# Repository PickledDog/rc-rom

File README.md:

# rc-rom
 ROM card for RC2014

(version 1.0 shown, current version 1.1 has a second LED for paging status)

## Overview
This RC2014-compatible board provides ROM from an EPROM or EEPROM, with 8k/16k/32k granularity. The ROM can be paged out and replaced by RAM, when combined with a compatible RAM card. A user-controllable LED is also provided.

## ROM
This board provides ROM to a RC2014 system. It does not provide RAM, but can interact with a compatible RAM card. The [official RC2014 64K RAM](https://rc2014.co.uk/modules/64k-ram/) card is supported, as is the [PD101 board](https://github.com/PickledDog/rc-z80ram), which it was designed in tandem with.

## Paging
Paging (the ability to replace the ROM with RAM) is implemented using the *PAGE* signal in the RC2014 Enhanced Bus. This is the only Enhanced Bus signal required - if you're using a Standard Bus backplane (or don't intend to install a two-row header), a wire can be used to link the page signals between this board and the RAM (the pin in question is #4 of the 10 Enhanced pins).

If the *PAGE* signal cannot be connected, any RAM in the system will need to be configured to not appear in the lower memory addresses used by the ROM - consult the documentation of the RAM board. PD101 *cannot* selectively disable memory like this, and requires the PAGE signal in order to work with this board. Alternatively, [PD106](https://github.com/PickledDog/rc-ramrom) can be built instead of this board, since it has RAM built-in and doesn't require the Enhanced bus.

## Software compatibility
The board presents two I/O devices to the system - the LED at base port 0x08, and the ROM paging at 0x38. The LED appears at the same address as the LED of the [SC114 Motherboard](https://smallcomputercentral.wordpress.com/sc114-documentation/), and the ROM control address is common to most Z80 retrocomputers (the official RC2014 RAM/ROM cards included). As such, this board is compatible with most SC114 software, as well as Grant Searle's CP/M loader. LED is active low (lights by default) - writing a **1** to 0x08 turns it off. Writing a **1** to 0x38 disables the ROM.

## Chip support
The board supports 27C64, 27C128, 27C256, and 27C512 EPROMs, as well as 28C64 and 28C256 EEPROMs. Other chips with similar pinouts will *probably* work, but are untested. 150ns parts (like most 28C256s) are running at the edge of their specification in a standard 7.3Mhz system, and may require lowering the CPU clock. The [27C256](https://www.mouser.com/ProductDetail/AT27C256R-70PU/), [27C512](https://www.mouser.com/ProductDetail/AT27C512R-70PU/), and [28C256](https://www.mouser.com/ProductDetail/AT28C256-15PU/) can be purchased new.

## Firmware
Most (if not all) [RC2014 ROM images](https://github.com/RC2014Z80/RC2014/tree/master/ROMs) can be used unmodified (selecting the right images for your serial board, of course). Stephen C Cousins' excellent [Small Computer Monitor](https://smallcomputercentral.wordpress.com/small-computer-monitor/) can be used as well - all of the R* configurations are supported. You will need an EPROM programmer (for example, a [TL866](https://www.ebay.com/sch/i.html?_nkw=tl866ii+plus)) to load the ROM images onto a chip.

## Jumper settings
Refer to the front of the board for detailed jumper setting instructions.

## Part selection
Bill Of Materials and part references are below. In order to make the 50-pin RC2014 Enhanced bus connector, you'll need to take a 2x40-pin right-angle header and pull out most of the pins from the top row (needle-nose pliers work well). I recommend using gold-plated header for this - I use these ones from [Pololu](https://www.pololu.com/product/2668) or [Sparkfun](https://www.sparkfun.com/products/12792). The jumper headers can be snapped from regular (or double-row) breakaway header, for which eBay is substantially cheaper; the Mouser listings are provided for convenience.

The specified parts are just the ones I used, and can be substituted as needed - Mouser links provided for convenience and reference. A ZIF socket can be used for the EPROM - these are best [sourced from eBay](https://www.ebay.com/sch/i.html?_nkw=28+pin+zif+socket).

| Reference | Value | Qty | Mouser link |
| --------- | ----- | --- | ----------- |
| C1-C4 | 100nF ceramic | 4 | [KEMET C315C104M5U5TA](https://www.mouser.com/ProductDetail/C315C104M5U5TA7303) |
| D1 | 3mm yellow LED | 1 | [Lite-On LTL-4251N](https://www.mouser.com/ProductDetail/LTL-4251N) |
| D2 | 3mm green LED | 1 | [Lite-On LTL-4231N](https://www.mouser.com/ProductDetail/LTL-4231N) |
| J1/2 | 2x40 right-angle header | 1 | [3M 2380-5121TG](https://www.mouser.com/ProductDetail/2380-5121TG) |
| JP1/2 | 2x3 header | 1 | [Amphenol 10129381-906002BLF](https://www.mouser.com/ProductDetail/10129381-906002BLF) |
| JP3/4/5 | 3x3 header | 1 | [Samtec TSW-103-07-L-T](https://www.mouser.com/ProductDetail/TSW-103-07-L-T) |
| JP6 | 2x2 header | 1 | [Amphenol 10129381-904002BLF](https://www.mouser.com/ProductDetail/10129381-904002BLF) |
| | jumpers | 7 | [Harwin M7583-46](https://www.mouser.com/ProductDetail/M7583-46)
| R1, R2 | 10kΩ resistor | 2 | [Yageo CFR-25JT-52-10K](https://www.mouser.com/ProductDetail/CFR-25JT-52-10K) |
| R3, R4 | 470Ω resistor | 2 | [Yageo CFR-25JT-52-470R](https://www.mouser.com/ProductDetail/CFR-25JT-52-470R) |
| U1 | EPROM | 1 | (see above for EPROM choices) |
| | socket | 1 | [Amphenol DILB28P-223TLF](https://www.mouser.com/ProductDetail/DILB28P-223TLF), or above ZIF |
| U2 | 74HCT138 | 1 | [TI SN74HCT138N](https://www.mouser.com/ProductDetail/SN74HCT138N) |
| U3 | 74HCT74 | 1 | [TI SN74HCT74N](https://www.mouser.com/ProductDetail/SN74HCT74N) |
| U4 | 74HCT4075 | 1 | [TI CD74HCT4075E](https://www.mouser.com/ProductDetail/CD74HCT4075E) |

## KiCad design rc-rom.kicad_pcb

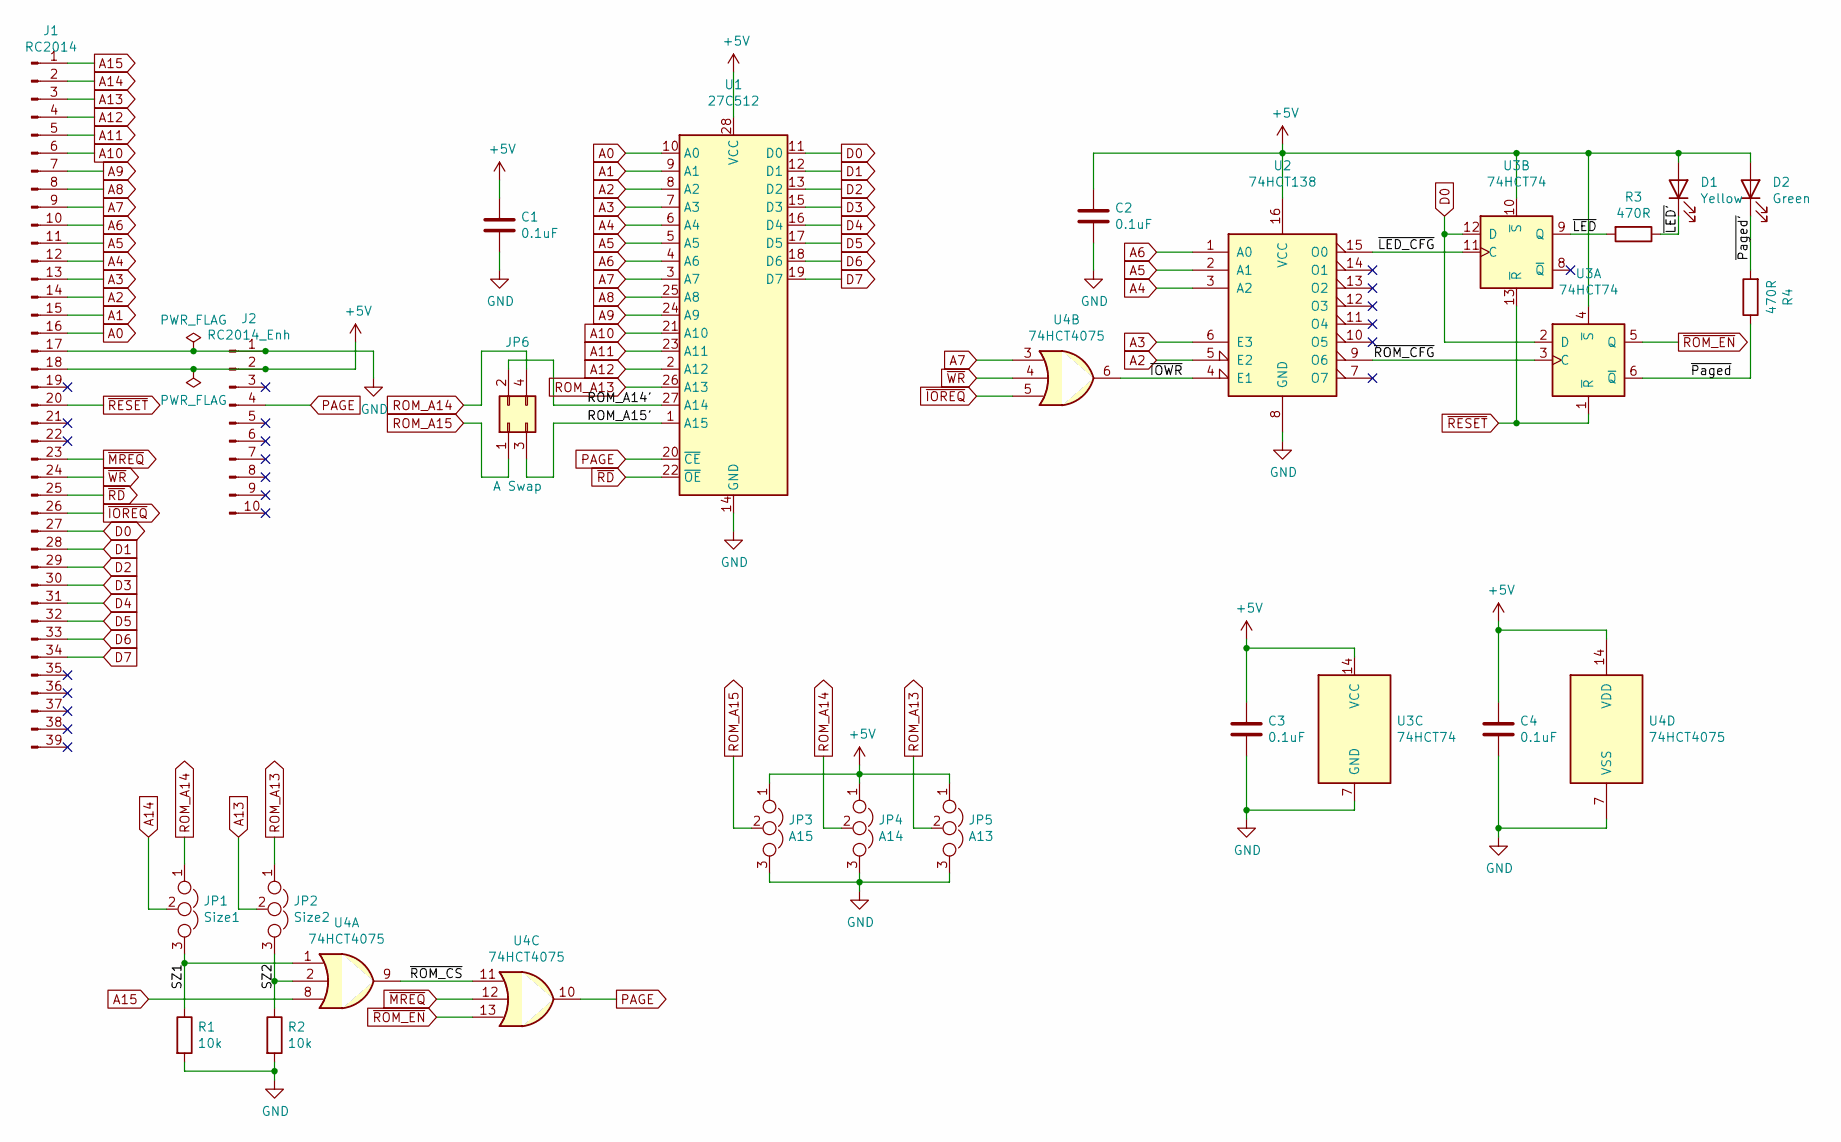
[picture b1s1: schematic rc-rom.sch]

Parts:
C1, C2, C3, C4: 0.1uF; C_Disc_D3.0mm_W1.6mm_P2.50mm
D1: Yellow; LED_D3.0mm
D2: Green; LED_D3.0mm
J1: RC2014; PinHeader_1x39_P2.54mm_Vertical
J2: RC2014_Enh; PinHeader_1x10_P2.54mm_Vertical
JP1: Size1; PinHeader_1x03_P2.54mm_Vertical
JP2: Size2; PinHeader_1x03_P2.54mm_Vertical
JP3: A15; PinHeader_1x03_P2.54mm_Vertical
JP4: A14; PinHeader_1x03_P2.54mm_Vertical
JP5: A13; PinHeader_1x03_P2.54mm_Vertical
JP6: A Swap; PinHeader_2x02_P2.54mm_Vertical
R1, R2: 10k; R_Axial_DIN0207_L6.3mm_D2.5mm_P7.62mm_Horizontal
R3, R4: 470R; R_Axial_DIN0207_L6.3mm_D2.5mm_P7.62mm_Horizontal
U1: 27C512; DIP_Socket-28_W11.9_W12.7_W15.24_W17.78_W18.5_3M_228-1277-0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
U2: 74HCT138; DIP-16_W7.62mm_LongPads
U3: 74HCT74; DIP-14_W7.62mm_LongPads
U4: 74HCT4075; DIP-14_W7.62mm_LongPads

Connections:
+5V: C1.1, C2.1, C3.1, C4.1, D1.2 (A), D2.2 (A), J1.18, J2.2, JP3.1, JP4.1, JP5.1, U1.28 (VCC), U2.16 (VCC), U3.4 (~S), U3.10 (~S), U3.14 (VCC), U4.14 (VDD)
/ROM_A14': JP6.2, U1.27 (A14)
/ROM_A15': JP6.3, U1.1 (A15)
/SZ1: JP1.3, R1.1, U4.1
/SZ2: JP2.3, R2.1, U4.2
/~IOWR: U2.4 (E1), U4.6
/~LED: R3.2, U3.9 (Q)
/~LED': D1.1 (K), R3.1
/~LED_CFG: U2.15 (O0), U3.11 (C)
/~Paged: R4.1, U3.6 (~Q)
/~Paged': D2.1 (K), R4.2
/~ROM_CFG: U2.9 (O6), U3.3 (C)
/~ROM_CS: U4.9, U4.11
A0: J1.16, U1.10 (A0)
A1: J1.15, U1.9 (A1)
A2: J1.14, U1.8 (A2), U2.5 (E2)
A3: J1.13, U1.7 (A3), U2.6 (E3)
A4: J1.12, U1.6 (A4), U2.3 (A2)
A5: J1.11, U1.5 (A5), U2.2 (A1)
A6: J1.10, U1.4 (A6), U2.1 (A0)
A7: J1.9, U1.3 (A7), U4.3
A8: J1.8, U1.25 (A8)
A9: J1.7, U1.24 (A9)
A10: J1.6, U1.21 (A10)
A11: J1.5, U1.23 (A11)
A12: J1.4, U1.2 (A12)
A13: J1.3, JP2.2
A14: J1.2, JP1.2
A15: J1.1, U4.8
D0: J1.27, U1.11 (D0), U3.2 (D), U3.12 (D)
D1: J1.28, U1.12 (D1)
D2: J1.29, U1.13 (D2)
D3: J1.30, U1.15 (D3)
D4: J1.31, U1.16 (D4)
D5: J1.32, U1.17 (D5)
D6: J1.33, U1.18 (D6)
D7: J1.34, U1.19 (D7)
GND: C1.2, C2.2, C3.2, C4.2, J1.17, J2.1, JP3.3, JP4.3, JP5.3, R1.2, R2.2, U1.14 (GND), U2.8 (GND), U3.7 (GND), U4.7 (VSS)
PAGE: J2.4, U1.20 (~CE), U4.10
ROM_A13: JP2.1, JP5.2, U1.26 (A13)
ROM_A14: JP1.1, JP4.2, JP6.4
ROM_A15: JP3.2, JP6.1
~IOREQ: J1.26, U4.5
~MREQ: J1.23, U4.12
~RD: J1.25, U1.22 (~OE)
~RESET: J1.20, U3.1 (~R), U3.13 (~R)
~ROM_EN: U3.5 (Q), U4.13
~WR: J1.24, U4.4

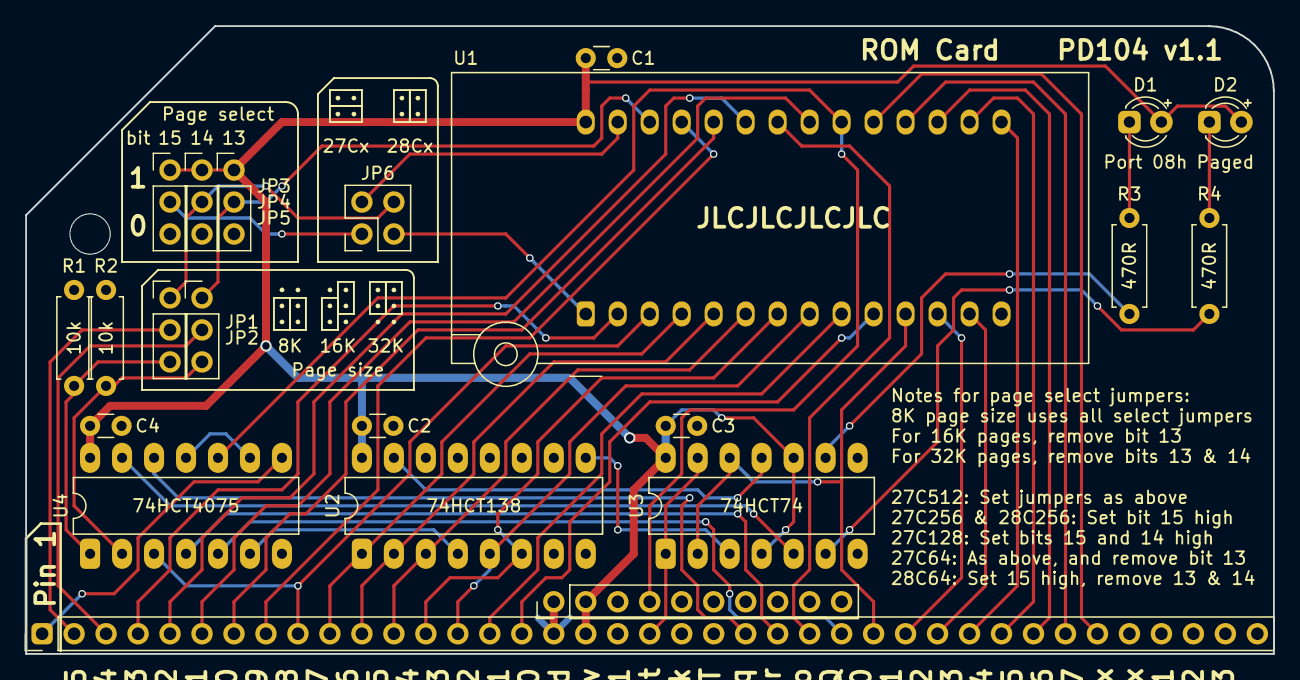
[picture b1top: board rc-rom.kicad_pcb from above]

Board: 2 copper layers, 99.1 x 49.9 mm, 22 parts (0 on the bottom side), 48 nets.

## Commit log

2020-11-27 Initial commit of rc-rom
    Initial commit of rc-rom/PD104
2020-12-02 Added silkscreen jumper diagrams, tweaked net labels
    Added reference diagrams for jumpers on the silkscreen, tweaked net labels
2020-12-09 Fix silk instructions
    Whoops the jumper instructions on the silk were wrong
2020-12-27 Added README, tidied up schematic and board
2020-12-30 Add board photos
2021-01-02 Moved to version 1.1, added LED for paging status
2021-01-06 Update silkscreen
2021-01-06 Fix README formatting
2021-01-24 Add rerefence to rc-ramrom
